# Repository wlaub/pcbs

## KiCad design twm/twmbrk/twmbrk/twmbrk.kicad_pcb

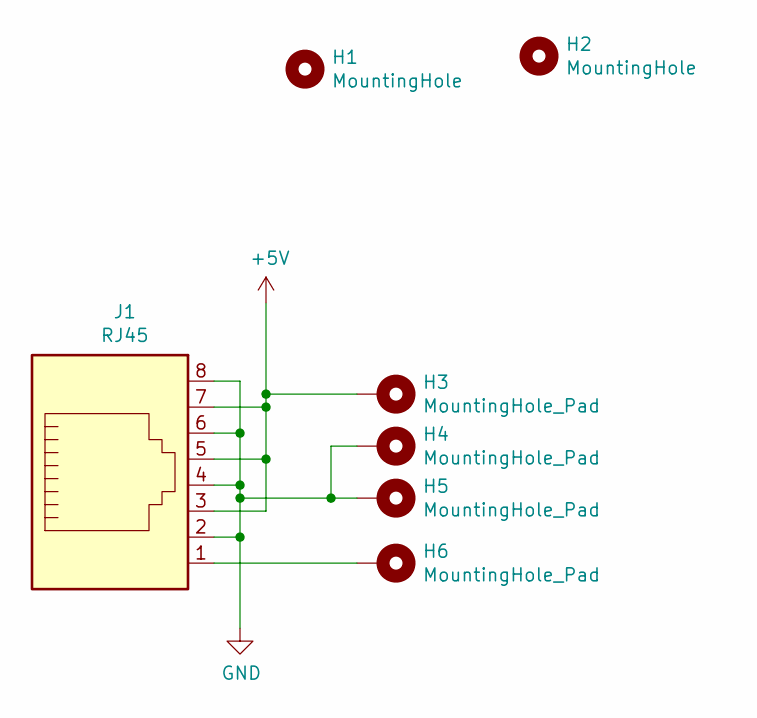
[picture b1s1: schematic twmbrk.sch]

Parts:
H1, H2: MountingHole; MountingHole_4.3mm_M4_Pad
H3, H4, H5, H6: MountingHole_Pad; Pin_D1.4mm_L8.5mm_W2.8mm_FlatFork
J1: RJ45; MJ3225-88-0

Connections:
+5V: H3.1, J1.3, J1.5, J1.7
GND: H1.1, H2.1, H4.1, H5.1, J1.2, J1.4, J1.6, J1.8
unnamed: H6.1, J1.1

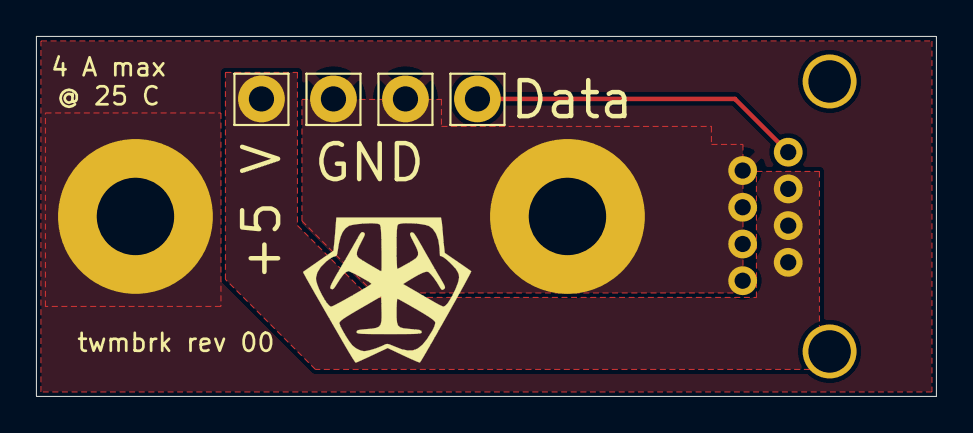
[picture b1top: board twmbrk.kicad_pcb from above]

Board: 2 copper layers, 50.0 x 20.0 mm, 7 parts (0 on the bottom side), 3 nets.

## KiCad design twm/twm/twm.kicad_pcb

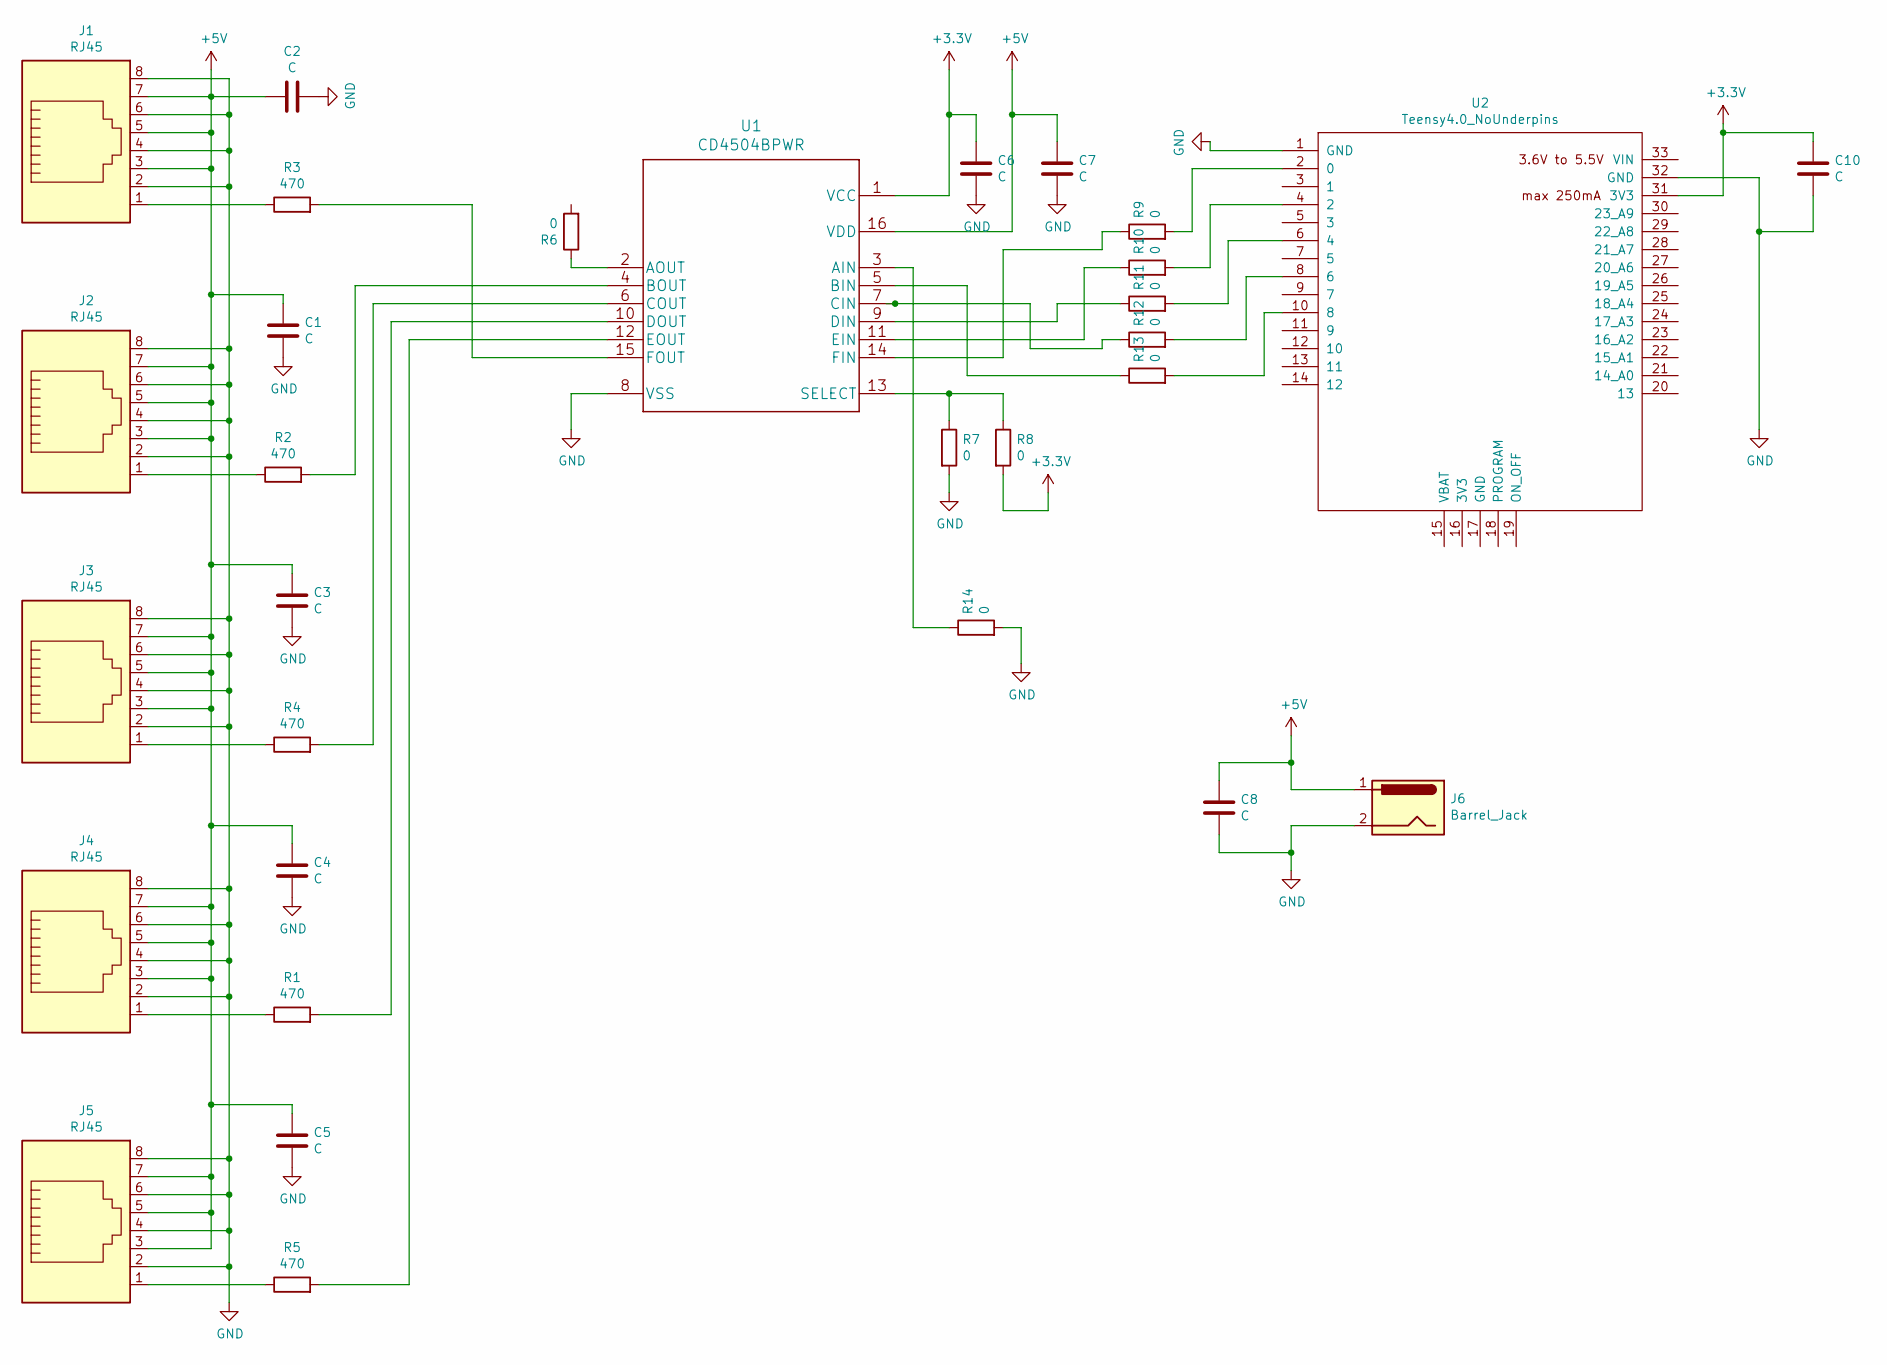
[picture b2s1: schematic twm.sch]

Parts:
C1, C2, C3, C4, C5, C8: C; C_0805_2012Metric_Pad1.15x1.40mm_HandSolder
C6, C7, C10: C; C_0603_1608Metric_Pad1.05x0.95mm_HandSolder
J1, J2, J3, J4, J5: RJ45; MJ3225-88-0
J6: Barrel_Jack; BarrelJack_CUI_PJ-063AH_Horizontal_CircularHoles
R1, R2, R3, R4, R5: 470; R_0603_1608Metric_Pad1.05x0.95mm_HandSolder
R6, R7, R8, R9, R10, R11, R12, R13, R14: 0; R_0603_1608Metric_Pad1.05x0.95mm_HandSolder
U1: CD4504BPWR
U2: Teensy4.0_NoUnderpins; Teensy40_outerpins

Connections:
+3V3: C6.1, C10.1, R8.2, U1.1 (VCC), U2.31 (3V3)
+5V: C1.1, C2.1, C3.1, C4.1, C5.1, C7.1, C8.1, J1.3, J1.5, J1.7, J2.3, J2.5, J2.7, J3.3, J3.5, J3.7, J4.3, J4.5, J4.7, J5.3, J5.5, J5.7, J6.1, U1.16 (VDD)
GND: C1.2, C2.2, C3.2, C4.2, C5.2, C6.2, C7.2, C8.2, C10.2, J1.2, J1.4, J1.6, J1.8, J2.2, J2.4, J2.6, J2.8, J3.2, J3.4, J3.6, J3.8, J4.2, J4.4, J4.6, J4.8, J5.2, J5.4, J5.6, J5.8, J6.2, R7.2, R14.2, U1.8 (VSS), U2.1 (GND), U2.32 (GND)
unnamed: J1.1, R3.1
unnamed: J2.1, R2.1
unnamed: J3.1, R4.1
unnamed: J4.1, R1.1
unnamed: J5.1, R5.1
unnamed: R1.2, U1.10 (DOUT)
unnamed: R2.2, U1.4 (BOUT)
unnamed: R3.2, U1.15 (FOUT)
unnamed: R4.2, U1.6 (COUT)
unnamed: R5.2, U1.12 (EOUT)
unnamed: R6.1, U1.2 (AOUT)
unnamed: R7.1, R8.1, U1.13 (SELECT)
unnamed: R9.1, U1.14 (FIN)
unnamed: R9.2, U2.2 (0)
unnamed: R10.1, U1.11 (EIN)
unnamed: R10.2, U2.4 (2)
unnamed: R11.1, U1.9 (DIN)
unnamed: R11.2, U2.6 (4)
unnamed: R12.1, U1.7 (CIN)
unnamed: R12.2, U2.8 (6)
unnamed: R13.1, U1.5 (BIN)
unnamed: R13.2, U2.10 (8)
unnamed: R14.1, U1.3 (AIN)

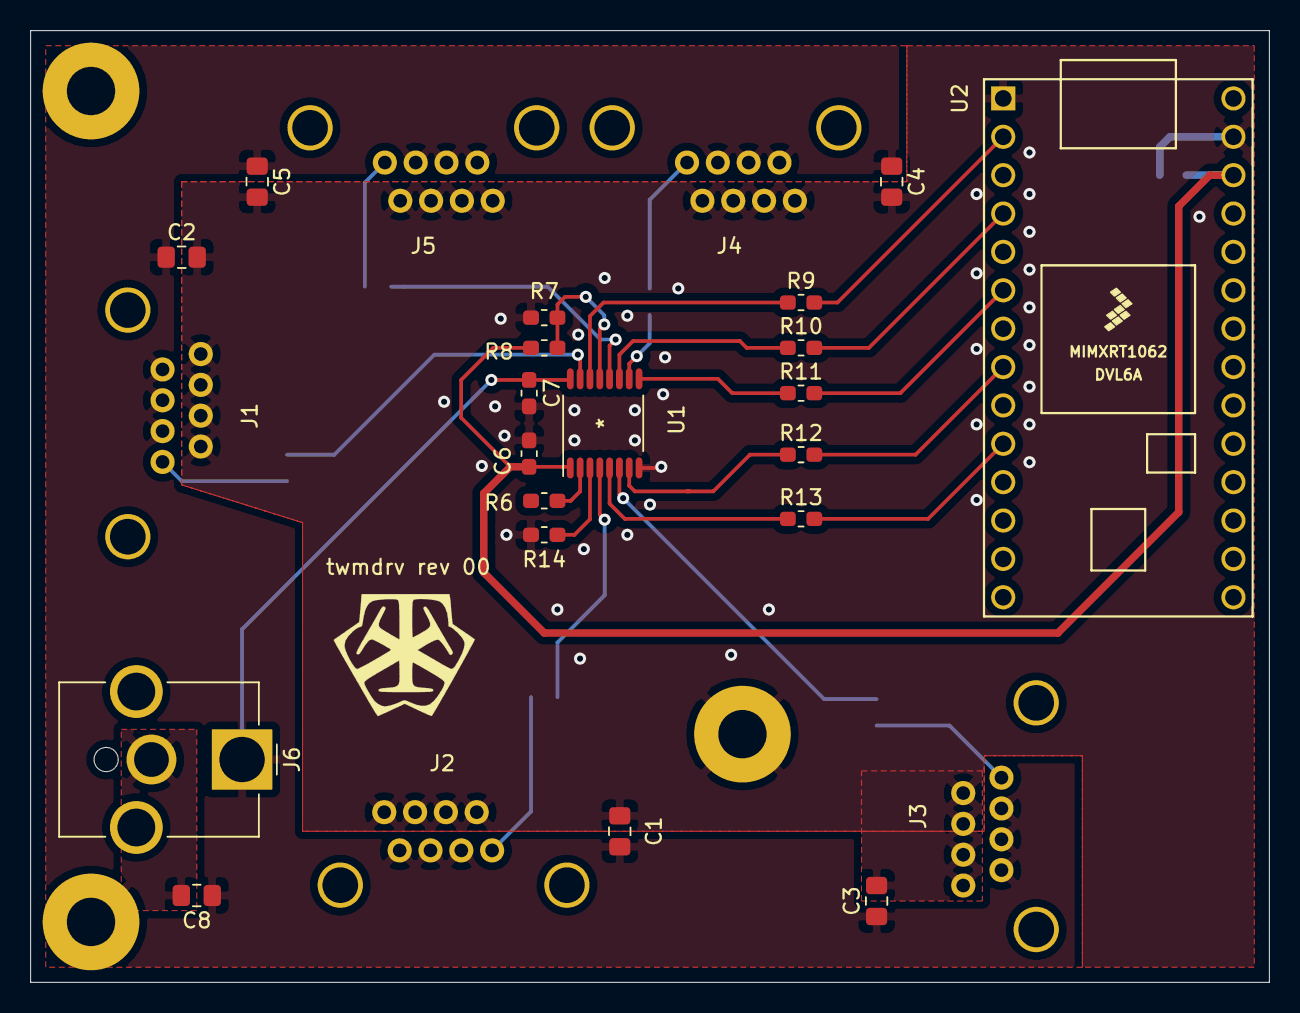
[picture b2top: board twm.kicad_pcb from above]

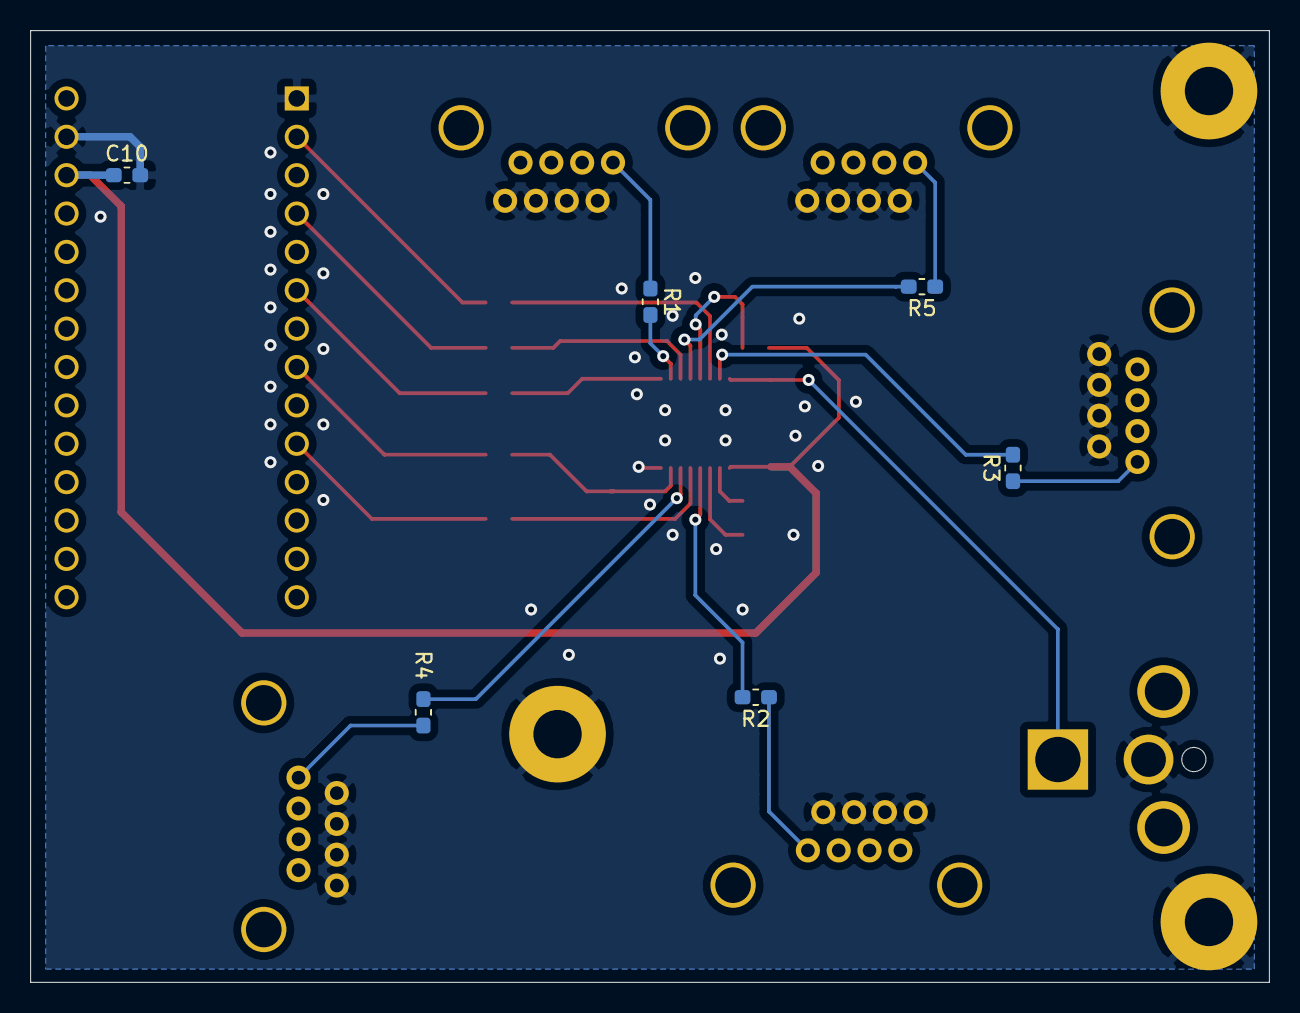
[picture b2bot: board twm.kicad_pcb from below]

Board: 2 copper layers, 82.0 x 63.0 mm, 31 parts (6 on the bottom side), 26 nets.

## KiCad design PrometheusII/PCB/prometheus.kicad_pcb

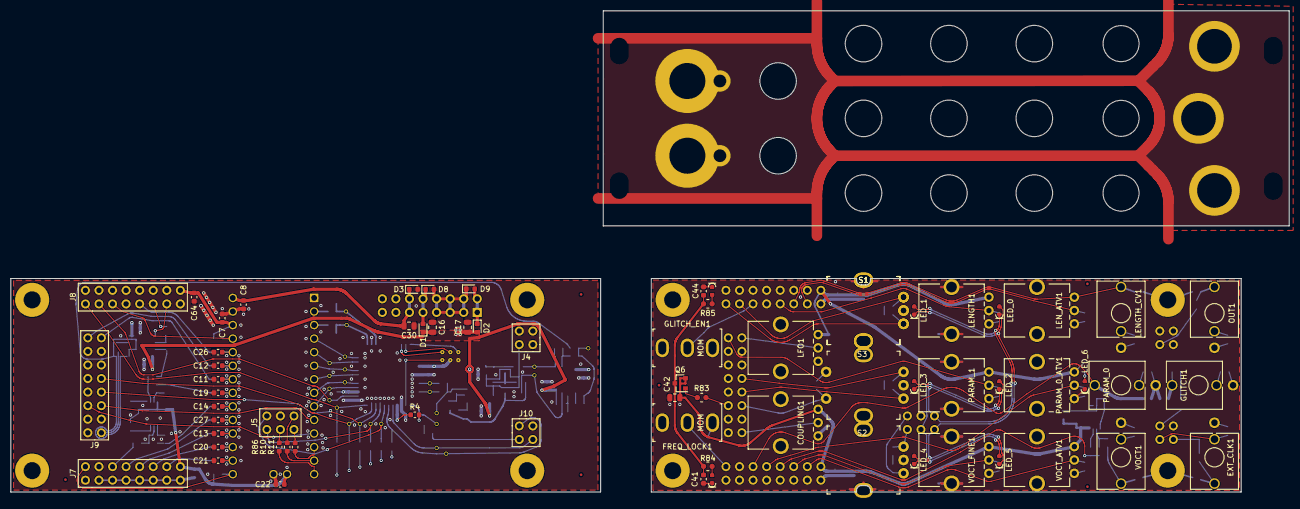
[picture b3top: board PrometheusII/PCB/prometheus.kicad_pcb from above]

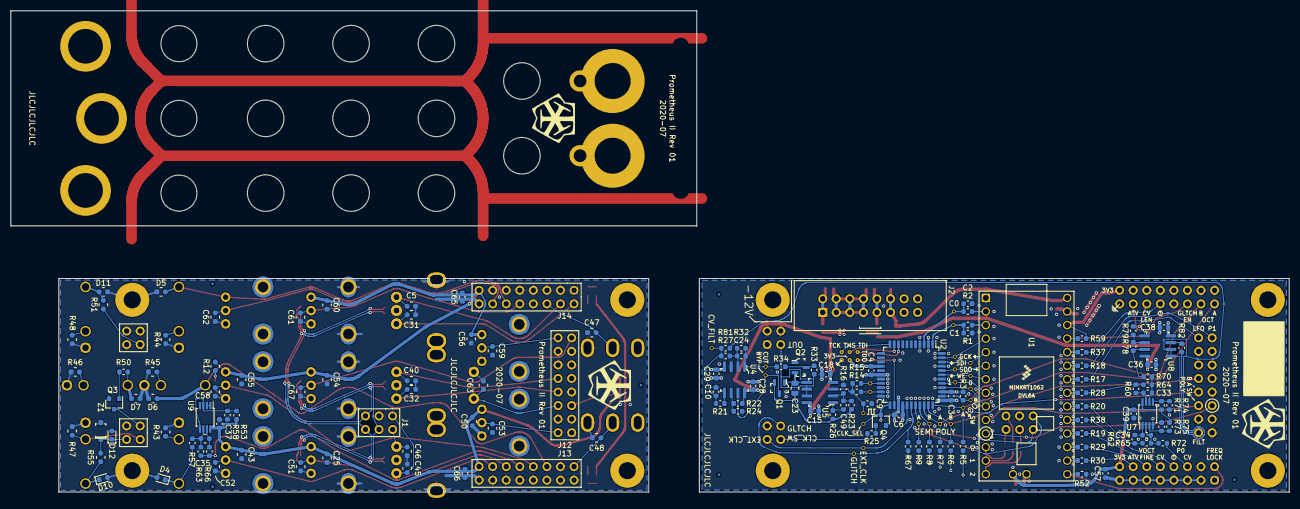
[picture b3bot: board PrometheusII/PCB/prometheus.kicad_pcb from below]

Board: 4 copper layers, 239.5 x 90.2 mm, 252 parts (143 on the bottom side), 136 nets.

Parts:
C1, C2, C9, C10, C24, C33, C34, C49: 1n; C_0603_1608Metric
C3, C4, C6, C7, C8, C15, C18, C22, C28, C29, C36, C37, C38, C39, C41, C44, C57, C64, C65, C66: 1u; C_0603_1608Metric
C5, C25, C31, C32, C40, C43, C45, C46, C47, C48, C50, C54, C55, C56, C60, C63: 100n; R_0603_RoundPads
C11, C12, C13, C14, C19, C20, C21, C26, C27: 100n; C_0603_1608Metric
C16, C17, C23, C30, C42: 10u; C_0805_2012Metric
C35, C51, C52, C53, C58, C59, C61, C62, C67: 1n; R_0603_RoundPads
COUPLING1: 100k; Fixed_Potentiometer_Bourns_PTV09A-1_Single_Vertical
D1, D2, D12: SD0603S040S0R2; D_0603_1608Metric
D3, D4, D8, D9, D10: D_TVS; D_0603_1608Metric
D5, D6, D7, D11: D_TVS; R_0603_RoundPads
EXT_CLK1: PJ398SM; Jack_3.5mm_QingPu_WQP-PJ398SM_Vertical_CircularHoles
FID1, FID2, FID3, FID4, FID5, FID6, FID7, FID8, FID9, FID10, FID11, FID12: Fiducial; Fiducial_0.5mm_Mask1mm
FREQ_LOCK1: TSM113F1; Toggle_Switch_TSM113F1
GLITCH1: PJ398SM; Jack_3.5mm_QingPu_WQP-PJ398SM_Vertical_CircularHoles
GLITCH_EN1: TSM113F1; Toggle_Switch_TSM113F1
H1, H2, H3, H4, H5, H6, H7, H8: R30-1001102; MountingHole_3.2mm_M3_Pad
J1, J5: Conn_02x03_Odd_Even; PinHeader_2x03_P2.54mm_Vertical
J2: Conn_02x08_Odd_Even; IDC-Header_2x08_P2.54mm_Vertical
J3, J4, J10, J11: Conn_02x02_Odd_Even; PinHeader_2x02_P2.54mm_Vertical
J7, J8, J9, J12, J13, J14: Conn_02x08_Odd_Even; PinHeader_2x08_P2.54mm_Vertical
LED_0, LED_1, LED_6: 150060AS75000; LED_0603_RoundPads
LED_2, LED_3, LED_4, LED_5: LTST-C190KGKT; LED_0603_RoundPads
LED_L1: LTST-C190KGKT; LED_0603_RoundPads
LED_R1: LTST-C190KGKT; LED_0603_RoundPads
LENGTH1: 100k; Fixed_Potentiometer_Bourns_PTV09A-1_Single_Vertical
LENGTH_CV1: PJ398SM; Jack_3.5mm_QingPu_WQP-PJ398SM_Vertical_CircularHoles
LEN_ATV1: 100k; Fixed_Potentiometer_Bourns_PTV09A-1_Single_Vertical
LFO1: 100k; Fixed_Potentiometer_Bourns_PTV09A-1_Single_Vertical
OUT1: PJ398SM; Jack_3.5mm_QingPu_WQP-PJ398SM_Vertical_CircularHoles
PARAM_0: PJ398SM; Jack_3.5mm_QingPu_WQP-PJ398SM_Vertical_CircularHoles
PARAM_0_ATV1, PARAM_1: 100k; Fixed_Potentiometer_Bourns_PTV09A-1_Single_Vertical
Q1, Q2: MMBF4391; SOT-23-3
Q3, Q4: BSS138; SOT-23
Q6: BSS84; SOT-23
R1, R2, R26: 25; R_0603_1608Metric
R3, R4, R5, R6, R7, R8, R9, R22, R32, R33, R34, R52, R59, R67, R70, R72, R78, R79: 100k; R_0603_1608Metric
R10, R11, R86: 330; R_0603_1608Metric
R12, R84, R85: 100; R_0603_RoundPads
R14, R15, R16: 10k; R_0603_1608Metric
R17, R18, R19, R20, R28, R29, R30, R37, R38, R60, R62, R66: 100; R_0603_1608Metric
R21, R82: 0; R_0603_1608Metric
R23: 20k; R_0603_1608Metric
R24, R65: 33k; R_0603_1608Metric
R25, R50, R81: 499; R_0603_1608Metric
R27: 22k; R_0603_1608Metric
R43: 10k; R_0603_RoundPads
R44, R45, R46, R47, R48: 100k; R_0603_RoundPads
R51, R55, R83: 499; R_0603_RoundPads
R53: 31.6k .1%; R_0603_1608Metric
R57: 100k .1%; R_0603_1608Metric
R58: 14.9k .1%; R_0603_1608Metric
R63: 56k .1%; R_0603_1608Metric
R64: 18k; R_0603_1608Metric
R71: 75k; R_0603_1608Metric
R73: 15k; R_0603_1608Metric
R74: 102k; R_0603_1608Metric
R75: 24.9k; R_0603_1608Metric
S1, S1#2, S2: PEC12R-4215F-N0012; Rotary_Encoder_Switched_PEC12R
S3: PEC11R-4215F-S0024; Rotary_Encoder_Switched_PEC11R
TP1, TP2, TP3, TP4, TP5, TP6, TP7, TP8, TP9, TP10, TP11, TP12, TP13, TP14, TP15, TP16, TP17, TP18, TP19, TP20, TP21, TP22, TP23: TestPoint; TestPoint_THTPad_D0.8mm_Drill0.5mm
TPJ1, TPJ2, TPJ3, TPJ4, TPJ5, TPJ6: TestPoint; TestPoint_THTPad_D0.8mm_Drill0.3mm
U1: Teensy4.0_NoSD; Teensy40_outerpins_extrasupply
U2: XC9572XL-10VQG44C_SLFSR; TQFP-44_10x10mm_P0.8mm
U4, U5, U8: TL072CDR; SOIC-8_W3.9mm
U7, U9: MCP6002-xMS; MSOP-8_3x3mm_P0.65mm
VOCT1: PJ398SM; Jack_3.5mm_QingPu_WQP-PJ398SM_Vertical_CircularHoles
VOCT_ATV1: 100k; Fixed_Potentiometer_Bourns_PTV09A-1_Single_Vertical
VOCT_FINE1: 100k; Fixed_Potentiometer_Bourns_PTV09A-1_Single_Vertical
Z1: MMSZ5231B-7-F; SOD-123

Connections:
+3V3: C3.1, C4.1, C6.1, C7.1, C22.2, C25.1, C37.2, C39.2, C42.1, C43.1, C50.1, C54.1, C55.1, C56.1, C57.2, C60.1, C64.2, C65.2, C66.2, COUPLING1.1, J7.16, J8.16, J13.15, J14.15, LENGTH1.1, LFO1.1, PARAM_0_ATV1.1, PARAM_1.1, Q6.2, R3.2, R4.2, R5.2, R6.2, R7.2, R8.2, R9.2, R12.2, R52.2, R53.2, R59.2, R67.2, R74.2, R75.2, TPJ1.1, U1.16, U1.31, U2.15, U2.26, U2.35, U7.8, U9.8, VOCT_ATV1.1, VOCT_FINE1.1
+5V: C8.1, C30.1, D3.1, J2.11, J2.12, U1.33
+12V: C15.2, C16.1, C28.2, C36.1, D1.1, R22.2, U4.8, U5.8, U8.8
-12V: C17.2, C18.1, C29.1, C38.2, D2.2, U4.4, U5.4, U8.4
/BYPASS: Q1.3, TP22.1, U4.7
/BYP_THRESH: R22.1, R24.2, U4.6
/CLK0: C2.1, R2.2, TP2.1, U2.3
/CLK0_T: R2.1, U1.2
/CLK1: C1.1, R1.2, TP1.1, U2.1
/CLK1_T: R1.1, U1.3
/CUTOFF: C24.1, R32.1, R34.1, TP23.1, U4.1
/CV_FILT: R81.2, U8.1, U8.2
/CV_FILT_P: C53.1, COUPLING1.2, J12.2
/EXT_CLK: J10.4, TP20.1, U2.27
/EXT_CLK_EN_T: Q4.3, R4.1, TP13.1, U2.23
/EXT_CLK_P: D12.1, J3.2, R55.1, Z1.K
/EXT_CLK_SW: J10.3, R25.2
/EXT_CLK_SW_P: EXT_CLK1.TN, J3.1, R47.2
/FB_OGAIN: C49.2, R16.2, R23.1, U5.2
/FREQ_LOCK_P: C48.1, FREQ_LOCK1.2, J13.1
/FREQ_LOCK_T: J7.2, R52.1, U1.20
/GLITCH_EN_P: C47.1, GLITCH_EN1.2, J14.6
/GLITCH_EN_T: J8.5, R59.1, U1.30
/GLITCH_IN_P: J3.3, Q3.3
/GLITCH_IN_T: J10.1, R67.1, TP19.1, U2.28
/JTAG_TCK: TPJ3.1, U2.11
/JTAG_TDI: TPJ5.1, U2.9
/JTAG_TDO: TPJ4.1, U2.24
/JTAG_TMS: TPJ2.1, U2.10
/LED_0_P: J1.6, LED_0.2, LED_1.1, LED_4.2, LED_5.1
/LED_0_T: R11.2, U1.12
/LED_1_P: J1.5, LED_0.1, LED_1.2, LED_2.2, LED_3.1
/LED_1_T: R10.2, U1.13
/LED_2_P: J1.4, LED_2.1, LED_3.2, LED_4.1, LED_5.2
/LED_2_T: R86.2, U1.14
/LEN_ATV: J8.13, U8.5
/LEN_ATV_P: C62.1, J14.14, LEN_ATV1.2
/LEN_CV: R28.1, R60.1, R64.1
/LEN_CV_P: D5.1, J14.12, LENGTH_CV1.T, LEN_ATV1.1
/LEN_CV_T: C19.1, R28.2, U1.26
/LEN_KNOB: J8.9, R37.1
/LEN_KNOB_P: C61.1, J14.10, LENGTH1.2
/LEN_KNOB_T: C26.1, R37.2, U1.29
/LFO: J9.15, R17.1
/LFO_LED_P: J12.5, R83.2
/LFO_LED_T: J9.6, U1.11
/LFO_P: C59.1, J12.16, LFO1.2
/LFO_T: C11.1, R17.2, U1.27
/LFSR0_IN: TP9.1, U1.9, U2.36
/LFSR1_IN: TP3.1, U1.8, U2.37
/OUT: J4.2, R33.2, U5.6, U5.7
/OUT0: R15.2, TP10.1, U2.21
/OUT1: R14.1, TP11.1, U2.19
/OUTA: C9.1, R14.2, R15.1, TP8.1, U5.3
/OUTB: C23.1, Q1.2, R23.2, R26.2
/OUTC: C23.2, Q1.1, Q2.2, U5.5
/OUT_P: J11.1, R51.1
/PARAM_0: J7.8, R38.1
/PARAM_0_CV: R20.1, R62.1, R65.1
/PARAM_0_CV_P: D6.1, J13.5, PARAM_0.T
/PARAM_0_CV_T: C14.1, R20.2, U1.25
/PARAM_0_P: C58.1, J13.7, PARAM_0_ATV1.2
/PARAM_0_T: C27.1, R38.2, U1.24
/PARAM_1: J9.16, R18.1
/PARAM_1_P: C67.1, J12.15, PARAM_1.2
/PARAM_1_T: C12.1, R18.2, U1.28
/POLY_A: J9.7, R7.1, TP16.1, U2.31
/POLY_A_P: C32.1, J12.8, S3.A
/POLY_B: J9.9, R6.1, TP15.1, U2.32
/POLY_B_P: C40.1, J12.10, S3.B
/POLY_SW: J9.5, U1.10
/POLY_SW_P: C63.1, J12.6, S3.1
/SCK: TP7.1, U1.4, U2.43
/SDI: TP6.1, U1.5, U2.42
/SDO: TP5.1, U1.6, U2.40
/VOCT_ATV: J7.14, R30.1
/VOCT_ATV_P: C52.1, J13.13, VOCT_ATV1.2
/VOCT_ATV_T: C21.1, R30.2, U1.21
/VOCT_CV: J7.10, R19.1
/VOCT_CV_P: J13.9, R63.1, R66.1
/VOCT_FINE: J7.12, R29.1
/VOCT_FINE_P: C51.1, J13.11, VOCT_FINE1.2
/VOCT_FINE_T: C20.1, R29.2, U1.22
/VOCT_OCT_A: J8.1, R5.1, TP14.1, U2.33
/VOCT_OCT_A_P: C31.1, J14.2, S1.A, S1#2.A
/VOCT_OCT_B: J8.3, R3.1, TP12.1, U2.34
/VOCT_OCT_B_P: C5.1, J14.4, S1.B, S1#2.B
/VOCT_SEMI_A: J5.2, R9.1, TP18.1, U2.29
/VOCT_SEMI_A_P: C45.1, J1.1, S2.A
/VOCT_SEMI_B: J5.1, R8.1, TP17.1, U2.30
/VOCT_SEMI_B_P: C46.1, J1.2, S2.B
/VOCT_T: C13.1, R19.2, U1.23
/WE: TP4.1, U1.7, U2.39
/_CV_FILT: J9.1, R82.2
/_LEN_CV: J8.11, R79.2
/_PARAM_0_CV: J7.6, R72.2
GND: C1.2, C2.2, C3.2, C4.2, C5.2, C6.2, C7.2, C8.2, C9.2, C10.2, C11.2, C12.2, C13.2, C14.2, C15.1, C16.2, C17.1, C18.2, C19.2, C20.2, C21.2, C22.1, C25.2, C26.2, C27.2, C28.1, C29.2, C30.2, C31.2, C32.2, C36.2, C37.1, C38.1, C39.1, C40.2, C41.2, C42.2, C43.2, C44.2, C45.2, C46.2, C47.2, C48.2, C50.2, C51.2, C52.2, C53.2, C54.2, C55.2, C56.2, C57.1, C58.2, C59.2, C60.2, C61.2, C62.2, C63.2, C64.1, C65.1, C66.1, C67.2, COUPLING1.3, D3.2, D4.2, D5.2, D6.2, D7.2, D8.2, D9.1, D10.2, D11.2, D12.2, EXT_CLK1.S, FREQ_LOCK1.1, FREQ_LOCK1.3, GLITCH1.S, GLITCH_EN1.1, GLITCH_EN1.3, H1.1, H2.1, H3.1, H4.1, H5.1, H6.1, H7.1, H8.1, J1.3, J2.3, J2.4, J2.5, J2.6, J2.7, J2.8, J3.4, J4.1, J4.3, J4.4, J5.4, J7.1, J7.3, J7.4, J7.5, J7.7, J7.9, J7.11, J7.13, J7.15, J8.2, J8.4, J8.6, J8.7, J8.8, J8.10, J8.12, J8.14, J8.15, J9.2, J9.3, J9.4, J9.8, J9.10, J9.11, J9.12, J9.13, J9.14, J10.2, J11.2, J11.3, J11.4, J12.1, J12.3, J12.4, J12.7, J12.9, J12.11, J12.12, J12.13, J12.14, J13.2, J13.3, J13.4, J13.6, J13.8, J13.10, J13.12, J13.14, J13.16, J14.1, J14.3, J14.5, J14.7, J14.8, J14.9, J14.11, J14.13, J14.16, LED_6.1, LED_L1.1, LED_R1.1, LENGTH1.3, LENGTH_CV1.S, LEN_ATV1.3, LFO1.3, OUT1.S, PARAM_0.S, PARAM_0_ATV1.3, PARAM_1.3, Q2.1, Q3.2, Q4.2, R16.1, R24.1, R43.1, R44.1, R45.1, R46.1, R47.1, R48.1, R58.1, R71.1, R73.1, S1.3, S1.C, S1#2.3, S1#2.C, S2.3, S2.C, S3.2, S3.3, S3.C, TPJ6.1, U1.1, U1.17, U1.32, U2.2, U2.4, U2.17, U2.18, U2.20, U2.22, U2.25, U2.38, U2.41, U4.3, U7.4, U9.4, VOCT1.S, VOCT_ATV1.3, VOCT_FINE1.3, Z1.A
unnamed: C10.1, R21.2, R27.2, R81.1, TP21.1
unnamed: C24.2, R27.1, R32.2, U4.2
unnamed: C33.1, R64.2, R70.1, U7.6
unnamed: C33.2, R60.2, U7.7
unnamed: C34.1, R65.2, R72.1, U7.2
unnamed: C34.2, R62.2, U7.1
unnamed: C35.1, R57.1, R63.2, U9.6
unnamed: C35.2, R66.2, U9.7
unnamed: C41.1, C44.1, Q6.3, R84.2, R85.2
unnamed: C49.1, R26.1, U5.1
unnamed: D1.2, D8.1, J2.9, J2.10
unnamed: D2.1, D9.2, J2.1, J2.2
unnamed: D4.1, R57.2, VOCT1.T
unnamed: D7.1, GLITCH1.T, R50.2
unnamed: D10.1, EXT_CLK1.T, R55.2
unnamed: D11.1, OUT1.T, R51.2
unnamed: GLITCH1.TN, R46.2
unnamed: J5.3, R86.1
unnamed: J5.5, R11.1
unnamed: J5.6, R10.1
unnamed: LED_6.2, R12.1
unnamed: LED_L1.2, R84.1
unnamed: LED_R1.2, R85.1
unnamed: LENGTH_CV1.TN, R44.2
unnamed: OUT1.TN, R48.2
unnamed: PARAM_0.TN, R45.2
unnamed: Q2.3, R33.1, R34.2
unnamed: Q3.1, R50.1
unnamed: Q4.1, R25.1
unnamed: Q6.1, R83.1
unnamed: R21.1, U4.5
unnamed: R43.2, VOCT1.TN
unnamed: R53.1, R58.2, U9.3, U9.5
unnamed: R70.2, R78.1, U8.7
unnamed: R71.2, R74.1, U7.5
unnamed: R73.2, R75.1, U7.3
unnamed: R78.2, R79.1, U8.6
unnamed: R82.1, U8.3
unnamed: U9.1, U9.2

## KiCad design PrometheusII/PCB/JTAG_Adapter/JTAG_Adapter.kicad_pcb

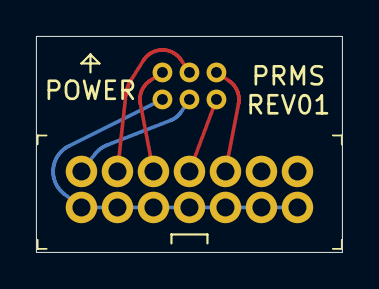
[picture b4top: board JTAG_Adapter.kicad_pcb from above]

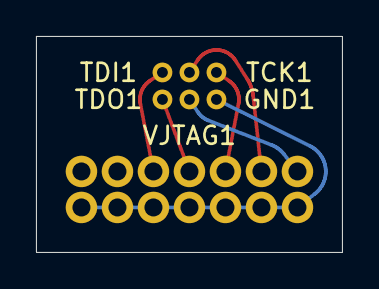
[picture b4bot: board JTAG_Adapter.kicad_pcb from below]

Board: 2 copper layers, 17.0 x 12.0 mm, 7 parts (6 on the bottom side), 6 nets.

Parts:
GND1: TestPoint; TestPoint_THTPad_D1.1mm_Drill0.6mm
J1: 0878311420; PinHeader_2x7_P2mm_Drill1mm
TCK1: TestPoint; TestPoint_THTPad_D1.1mm_Drill0.6mm
TDI1: TestPoint; TestPoint_THTPad_D1.1mm_Drill0.6mm
TDO1: TestPoint; TestPoint_THTPad_D1.1mm_Drill0.6mm
TMS1: TestPoint; TestPoint_THTPad_D1.1mm_Drill0.6mm
VJTAG1: TestPoint; TestPoint_THTPad_D1.1mm_Drill0.6mm

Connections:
+3V3: J1.2, VJTAG1.1
/JTAG_TCK: J1.6, TCK1.1
/JTAG_TDI: J1.10, TDI1.1
/JTAG_TDO: J1.8, TDO1.1
/JTAG_TMS: J1.4, TMS1.1
GND: GND1.1, J1.1, J1.3, J1.5, J1.7, J1.9, J1.11, J1.13

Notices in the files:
parts and their libraries:
Copyright 2021 Accelerated Designs. All rights reserved.
